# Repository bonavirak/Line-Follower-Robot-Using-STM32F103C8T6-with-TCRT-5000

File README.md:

# Line Follower Robot with STM32F103C8T6 and TCRT5000

This Line Follower Robot, winner of Line Follwer Robot Competition 2025, was designed and developed by Bona Virak. The project uses an STM32F103C8T6 microcontroller, TCRT5000 5-way sensors, HC-05 Bluetooth module, TB6612FNG motor driver, and N20 motors (1000 RPM). It features two modes: Auto (PID-based line following with Case 0/Case 1 logic) and Manual (Bluetooth RC control via app).

## Credits
- **Author**: [Bona Virak](https://github.com/bonavirak) - Sole developer of the code, PCB design, and implementation.
- **Team**: Tire-d - Acknowledged for participation in Line Follwer Robot Competition 2025, with minimal contributions.

## Features
- C-based firmware with PID control for auto mode line following.
- Manual mode for Bluetooth RC car control via HC-05.
- PCB design (schematics, Gerber files, BOM) optimized for STM32 integration.
- Case-based navigation (Case 0 for straight paths, Case 1 for turns) in auto mode.

## Setup
### Hardware
1. **Components**:
   - STM32F103C8T6 microcontroller
   - TCRT5000 5-way sensor array
   - HC-05 Bluetooth module
   - TB6612FNG motor driver
   - 2x N20 motors (1000 RPM)
   - Power supply (e.g., 11.1V LiPo battery)
2. **Schematic**:
   - See schematic: 
3. **Wiring**:
- **Connect TCRT5000 Sensors to STM32**:
  - Pins: **PA0-PA4** 
- **Link HC-05 TX/RX to STM32**:
  - USART1: **PA9/PA10** (TX/RX) 
- **Attach TB6612FNG PWM/GPIO Pins to STM32**:
  - PWMA: **PB7**  (TIM4 CH2)
  - PWMB: **PB6**  (TIM4 CH1)
  - AI1: **PB12** 
  - AI2: **PB13** 
  - BI1: **PB14** 
  - BI2: **PB15** 
  - STBY: **PB1** 
  - VCC: **3.3V** 
- **Add Servo to STM32**:
  - PWM: **PB4** (TIM3 CH1) 
- **Wire N20 Motors to TB6612FNG Outputs**:
  - Power: **11.1V LiPo** 
- **Refer to Detailed Pin Assignments**:
  - Check out the epic diagram! 

### Software
1. **Requirements**:
   - STM32CubeIDE for compiling C code.
   - ST-Link/V2 for flashing.
   - Bluetooth RC app (e.g., "Bluetooth RC Controller" on Android) for manual mode.
2. **Steps**:
   - Clone: git clone: https://github.com/bonavirak/STM32F103C8T6-Line-Follower-Robot-TCRT5000.git.
   - Open `/code/` in STM32CubeIDE.
   - Configure PID in `pid.c` (e.g., Kp=0.5, Ki=0.1, Kd=0.05) for auto mode.
   - Build/flash code to STM32F103C8T6 using ST-Link.
3. **Auto Mode**:
   - Test Case 0/Case 1 on sample map 
4. **Manual Mode**:
   - Pair HC-05 with Bluetooth RC app (default PIN: 1234 or 0000).
   - Use app to control motors (forward, backward, left, right).

## Demo
Watch the robot in action:
- **Video**: [Video demo will be added soon!]
- **Images**: [Soon!]
- **Description**: Auto mode uses PID control for line following (Case 0 for straight, Case 1 for turns). Manual mode allows RC car control via Bluetooth app, demonstrated in Line Follwer Robot Competition 2025 winning run.

## License
Licensed under the MIT License. See [LICENSE](LICENSE) for details.

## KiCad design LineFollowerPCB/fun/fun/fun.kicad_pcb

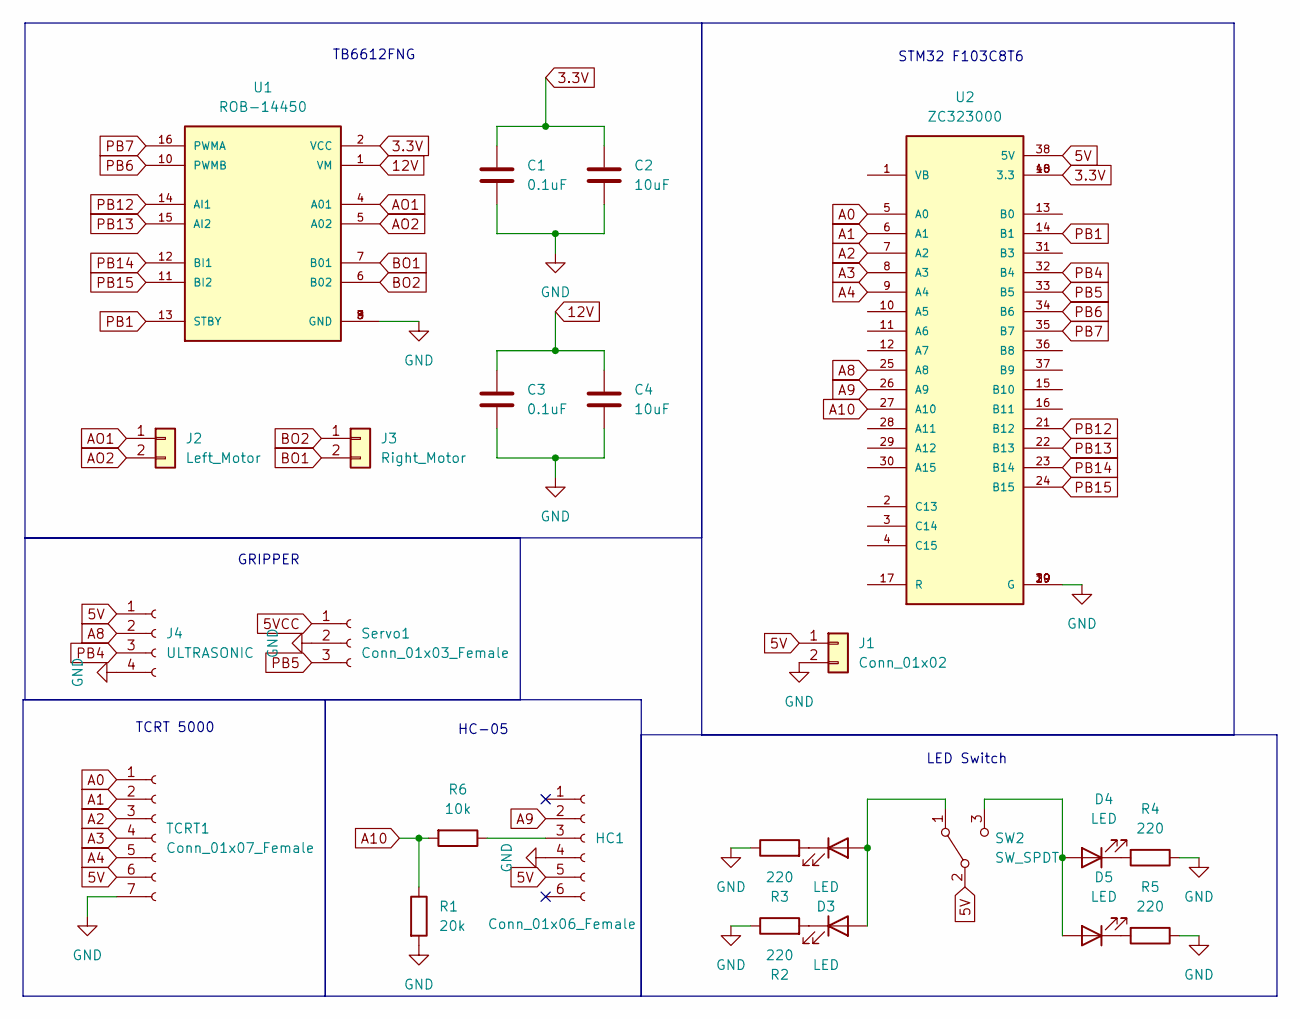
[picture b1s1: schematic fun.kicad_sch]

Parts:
C1, C3: 0.1uF; C_0603_1608Metric
C2, C4: 10uF; C_0603_1608Metric
D2, D3, D4, D5: LED; LED_D3.0mm
HC1: Conn_01x06_Female; PinSocket_1x06_P2.54mm_Vertical
J1: Conn_01x02; PinSocket_1x02_P2.54mm_Vertical
J2: Left_Motor; PinSocket_1x02_P2.54mm_Vertical
J3: Right_Motor; PinSocket_1x02_P2.54mm_Vertical
J4: ULTRASONIC; PinSocket_1x04_P2.54mm_Vertical
R1: 20k; R_0201_0603Metric
R2, R3, R4, R5: 220; R_0201_0603Metric
R6: 10k; R_0201_0603Metric
SW2: SW_SPDT; PinHeader_1x03_P2.54mm_Vertical
Servo1: Conn_01x03_Female; PinSocket_1x03_P2.54mm_Vertical
TCRT1: Conn_01x07_Female; PinSocket_1x07_P2.54mm_Vertical
U1: ROB-14450; MODULE_ROB-14450; PARTREV 11-13-17
U2: ZC323000; STM32F103C8T6; PARTREV N/A

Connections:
3.3V: C1.1, C2.1, U1.2 (VCC), U2.18 (3.3), U2.40 (3.3)
5V: HC1.5, J1.1, J4.1, SW2.2 (B), TCRT1.6, U2.38 (5V)
5VCC: Servo1.1
12V: C3.1, C4.1, U1.1 (VM)
A0: TCRT1.1, U2.5 (A0)
A1: TCRT1.2, U2.6 (A1)
A2: TCRT1.3, U2.7 (A2)
A3: TCRT1.4, U2.8 (A3)
A4: TCRT1.5, U2.9 (A4)
A8: J4.2, U2.25 (A8)
A9: HC1.2, U2.26 (A9)
A10: R1.1, R6.2, U2.27 (A10)
AO1: J2.1, U1.4 (A01)
AO2: J2.2, U1.5 (A02)
BO1: J3.2, U1.7 (B01)
BO2: J3.1, U1.6 (B02)
GND: C1.2, C2.2, C3.2, C4.2, HC1.4, J1.2, J4.4, R1.2, R2.1, R3.1, R4.1, R5.1, Servo1.2, TCRT1.7, U1.3 (GND), U1.8 (GND), U1.9 (GND), U2.19 (G), U2.20 (G), U2.39 (G)
unnamed: D2.2 (A), D3.2 (A), SW2.1 (A)
unnamed: D2.1 (K), R2.2
unnamed: D3.1 (K), R3.2
unnamed: D4.2 (A), D5.2 (A), SW2.3 (C)
unnamed: D4.1 (K), R4.2
unnamed: D5.1 (K), R5.2
unnamed: HC1.3, R6.1
PB1: U1.13 (STBY), U2.14 (B1)
PB4: J4.3, U2.32 (B4)
PB5: Servo1.3, U2.33 (B5)
PB6: U1.10 (PWMB), U2.34 (B6)
PB7: U1.16 (PWMA), U2.35 (B7)
PB12: U1.14 (AI1), U2.21 (B12)
PB13: U1.15 (AI2), U2.22 (B13)
PB14: U1.12 (BI1), U2.23 (B14)
PB15: U1.11 (BI2), U2.24 (B15)

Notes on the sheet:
GRIPPER
LED Switch
HC-05
TB6612FNG
STM32 F103C8T6
TCRT 5000

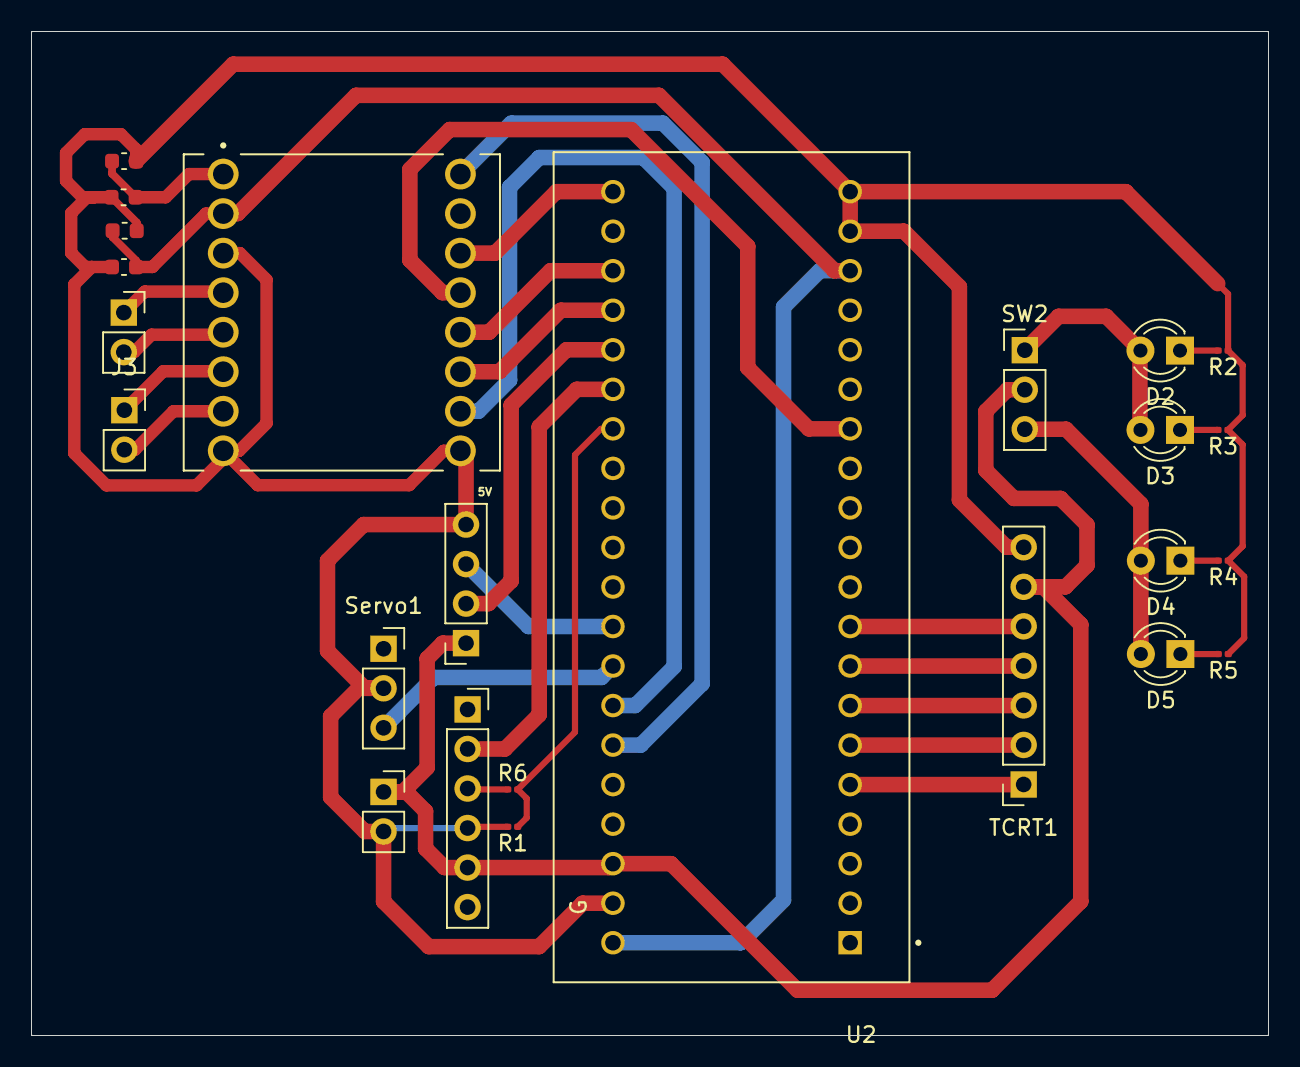
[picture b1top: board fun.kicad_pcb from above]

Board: 2 copper layers, 79.5 x 64.5 mm, 24 parts (0 on the bottom side), 32 nets.

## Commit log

2025-08-15 Update LICENSE
2025-08-16 Create Line Follower
2025-08-16 Create Core
2025-08-16 Create Inc
2025-08-16 Update Core
2025-08-19 Files
2025-08-19 README.md
